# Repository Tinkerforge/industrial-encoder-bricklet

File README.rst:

Industrial Encoder Bricklet
===========================

**This Bricklet is currently in development.**

This repository contains the firmware source code and the hardware design
files. The documentation generator configs can be found at
https://github.com/Tinkerforge/generators

Repository Content
------------------

software/:
 * examples/: Examples for all supported languages
 * build/: Compiled files
 * src/: Source code of firmware
 * Makefile: Makefile to build project

hardware/:
 * Contains KiCad project files and additionally schematics as PDF

datasheets/:
 * Contains datasheets for sensors and complex ICs that are used

Hardware
--------

The hardware is designed with the open source EDA Suite KiCad
(http://www.kicad.org). Before you are able to open the files,
you have to install the Tinkerforge kicad-libraries
(https://github.com/Tinkerforge/kicad-libraries). You can either clone
them directly in hardware/ or clone them in a separate folder and
symlink them into hardware/
(ln -s kicad_path/kicad-libraries project_path/hardware). After that you
can open the .pro file in hardware/ with KiCad and from there view and
modify the schematics and the PCB layout.

Software
--------

If you want to do your own Brick/Bricklet firmware development we highly
recommend that you use our build environment setup script and read the
tutorial (https://www.tinkerforge.com/en/doc/Tutorials/Tutorial_Build_Environment/Tutorial.html).

To compile the C code we recommend you to install the newest GNU Arm Embedded
Toolchain (https://launchpad.net/gcc-arm-embedded/+download).
You also need to install bricklib2 (https://github.com/Tinkerforge/bricklib2).

You can either clone it directly in software/src/ or clone it in a
separate folder and symlink it into software/src/
(ln -s bricklib_path/bricklib2 project_path/software/src/). Finally make sure to
have CMake installed (http://www.cmake.org/cmake/resources/software.html).

After that you can build the firmware by invoking make in software/.
The firmware (.zbin) can then be found in software/build/ and uploaded
with brickv (click button "Flashing" on start screen).

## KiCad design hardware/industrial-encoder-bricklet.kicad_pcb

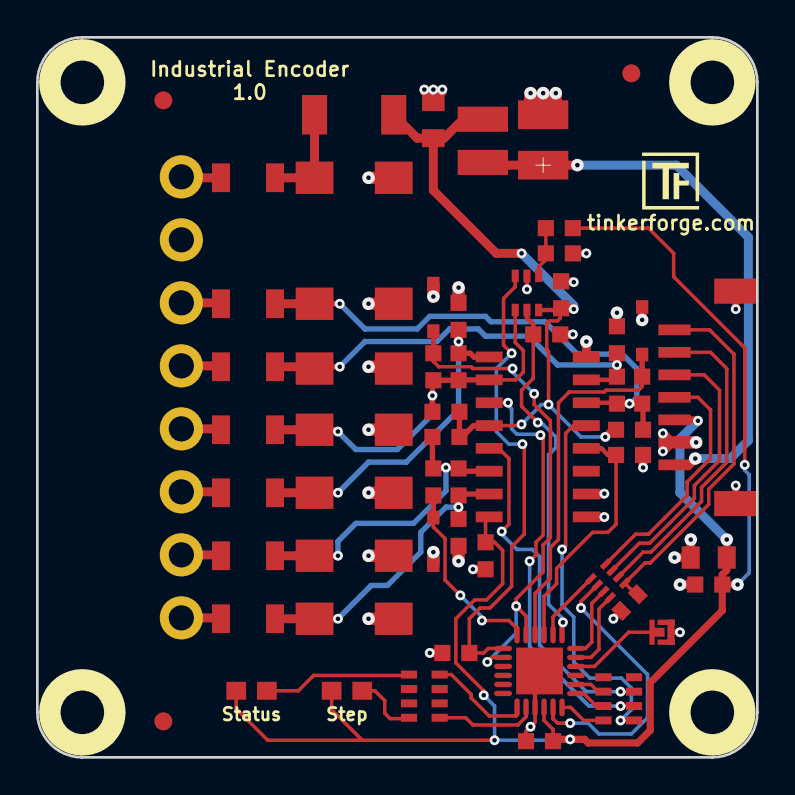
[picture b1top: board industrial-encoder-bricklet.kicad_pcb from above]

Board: 2 copper layers, 40.0 x 40.0 mm, 63 parts (1 on the bottom side), 44 nets.

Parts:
C1: TBD; C0402E
C2: 10uF; C0805
C3, C5, C6: 100nF; C0603F
C4: 1uF; C0603F
C7: 100µF; 3528-21
C8: 10µF; C0805
D1: LED blue; D0603E
D2: LED green; D0603E
D3, D4, D11: ESD3V3D3B-TP; SOD-323
D5: PMEG6050; SOD-128
D6, D7, D8, D9, D10, D12, D13: SMAJ5.0CA; DO-214AC
Fiducial_Mark: VAL**; Fiducial_Mark
Fiducial_Mark#2, Fiducial_Mark#3: VAL**; Fiducial_Mark
L1: 6.8uH; WE-LQ-1210
P1: CON-SENSOR; CON-SENSOR2
P2: Boot; SolderJumper
P3: CONN_8; OQ_8P
R1, R2, R3, R4, R5, R8, R10, R11, R13, R22, R24: 1k; R0603F
R6, R7, R15: 100; R0603F
R9, R12, R23: 150; R0603F
R14, R16, R17, R18, R19, R20, R21: 10; R1206
RP1: TBD; 4X0402
RP2, RP3: 1k; 0603X4
U1: XMC1XXX24; QFN24-4x4mm-0.5mm
U2: OPA358; SC70-6
U3: ISL32173E; SOIC16
U4, U5, U6, U7: DRILL; DRILL_NP
VAL: CE_5mm

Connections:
+5V: C7.1, L1.1, P1.1
+5VA: C5.1, C8.2, D5.1, L1.2, R8.2, R11.2, R22.2, U2.6, U3.12
A-D: RP3.5, U3.5
A-T: D3.2, R6.1, U1.22
A/DAT: D7.1, R6.2, R8.1, R9.2, R16.2, U3.6
B-CLK: R1.2, U1.1, U2.3
B-CLK-EN: R2.2, U1.19, U2.5
B-D: RP3.6, U3.11
B-T: D4.2, R7.1, U1.2, U1.23
B/CLK: D9.1, R7.2, R11.1, R12.2, R18.2, U2.4, U3.10
EN-DIFF: R5.2, U1.21, U3.4
GND: C1.1, C2.1, C3.1, C4.1, C5.2, C6.2, C7.2, C8.1, D3.1, D4.1, D6.2, D7.2, D8.2, D9.2, D10.2, D11.1, D12.2, D13.2, P1.2, P1.EP, P2.1, P3.2, R1.1, R2.1, R4.1, R5.1, R10.1, R13.1, R24.1, U1.9, U1.EXP, U2.2, U3.1, U3.2, U3.8
I: D12.1, R15.2, R20.2, R22.1, R23.2, U3.14
I-D: RP3.7, U3.13
I-T: D11.2, R15.1, U1.24
unnamed: C1.2, P1.7, RP1.5
unnamed: D1.2, RP2.1
unnamed: D2.2, RP2.4
unnamed: D5.2, D6.1, R14.2
unnamed: P1.4, RP1.8
unnamed: P1.5, RP1.7
unnamed: P1.6, RP1.6
unnamed: P2.2, U1.16
unnamed: P3.1, R14.1
unnamed: P3.3, R16.1
unnamed: P3.4, R17.1
unnamed: P3.5, R18.1
unnamed: P3.6, R19.1
unnamed: P3.7, R20.1
unnamed: P3.8, R21.1
unnamed: R3.1, R4.2, U2.1
unnamed: RP2.5, U1.8
unnamed: RP2.8, U1.7
unnamed: RP3.2, U1.14
unnamed: RP3.3, U1.13
unnamed: RP3.4, U1.12
S-CLK: RP1.2, U1.11
S-CS: RP1.1, U1.20
S-MISO: RP1.4, U1.17
S-MOSI: RP1.3, U1.18
VCC: C2.2, C3.2, C4.2, C6.1, D1.1, D2.1, P1.3, R3.2, U1.10, U3.16
~A: D8.1, R9.1, R10.2, R17.2, U3.7
~B: D10.1, R12.1, R13.2, R19.2, U3.9
~I: D13.1, R21.2, R23.1, R24.2, U3.15

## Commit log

2017-02-13 add data files for new industrial encoder bricklet
2017-05-05 fix filter circuit, not completly finished
2017-05-08 schematic fixed
2017-05-18 define inductor, update footprints
2017-06-02 fix 5V connection error of ISL
2017-07-28 Add 3d information (final)
2017-07-28 Add 3d model (*.step & *.FCStd)
2017-07-28 Fix 3d model of WE_LQ_1210
2018-02-20 Add .gitignore
2018-02-20 Cleanup KiCad libraries config
    Ensure LibDir=kicad-libraries and LibName1=tinkerforge.
    Remove special library.
2018-05-11 Rename files
2018-06-28 Fix readme
2018-07-11 Add Makefile with docker support
2018-07-13 Fix compile instructions
2021-10-25 Update KiCad link
    https://www.kicad.org/blog/2021/10/Avoid-links-to-former-kicad-domain/
2022-07-06 Add license files.

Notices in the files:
hardware/industrial-encoder-bricklet.kicad_pcb:
Licensed under CERN OHL v.1.1
Copyright (©) 2017, B.Nordmeyer
Copyright Tinkerforge GmbH 2017.
This documentation describes Open Hardware and is licensed under the
CERN OHL v. 1.1.
